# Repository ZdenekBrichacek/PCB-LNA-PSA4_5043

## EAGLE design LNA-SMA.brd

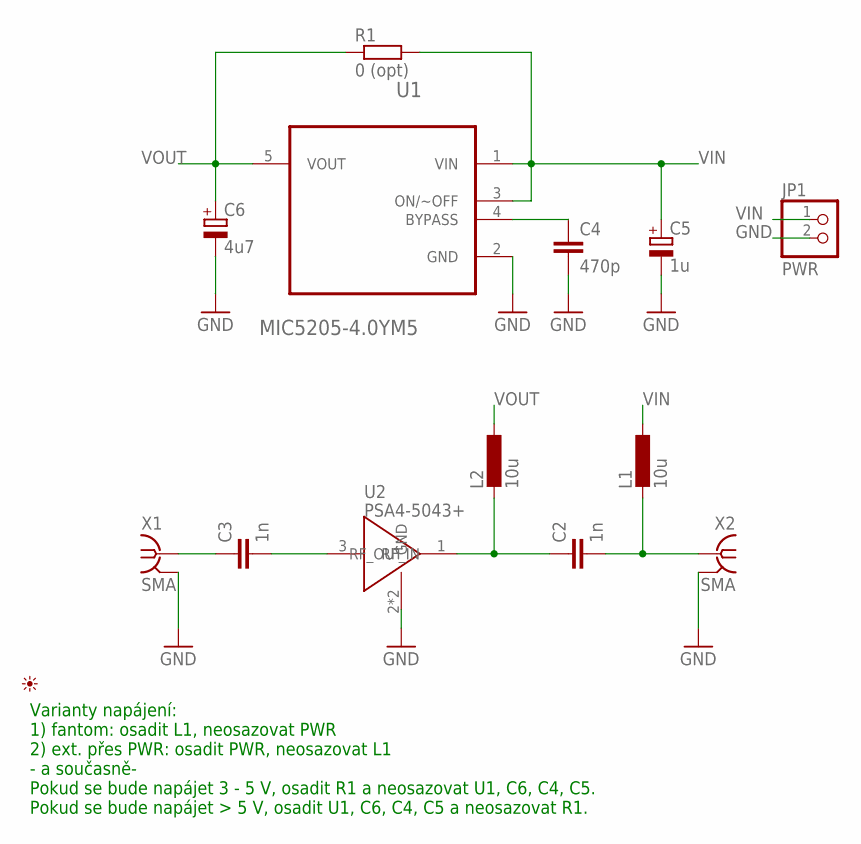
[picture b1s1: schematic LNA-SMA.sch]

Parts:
C2, C3: 1n; C0603
C4: 470p; C0603
C5: 1u; SMC_A
C6: 4u7; SMC_A
JP1: PWR; 1X02
L1, L2: 10u; L2012C
R1: 0 (opt); R0603
U1: MIC5205-4.0YM5; SOT95P280X145-5N
U2: PSA4-5043+; INF-SOT343_V_1PRIMARY
U$1: PICTO_1
X1, X2: SMA; J502-ND-142-0701-801/806

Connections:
GND: C4.2, C5.-, C6.-, JP1.2, U1.2 (GND), U2.2 (GND), U2.4 (GND), X1.G@1 (2), X1.G@2 (2), X1.G@3 (2), X1.G@4 (2), X2.G@1 (2), X2.G@2 (2), X2.G@3 (2), X2.G@4 (2)
unnamed: C4.1, U1.4 (BYPASS)
unnamed: C3.2, U2.3 (RF_IN)
unnamed: C2.1, L2.2, U2.1 (RF_OUT)
RF_IN: C2.2, L1.2, X2.1
RF_OUT: C3.1, X1.1
VIN: C5.+, JP1.1, L1.1, R1.2, U1.1 (VIN), U1.3 (ON/~OFF)
VOUT: C6.+, L2.1, R1.1, U1.5 (VOUT)

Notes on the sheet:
Varianty napájení: 1) fantom: osadit L1, neosazovat PWR 2) ext. přes PWR: osadit PWR, neosazovat L1 - a současně- Pokud se bude napájet 3 - 5 V, osadit R1 a neosazovat U1, C6, C4, C5. Pokud se bude napájet > 5 V, osadit U1, C6, C4, C5 a neosazovat R1.

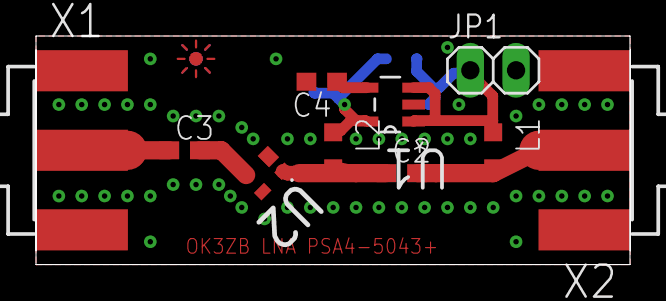
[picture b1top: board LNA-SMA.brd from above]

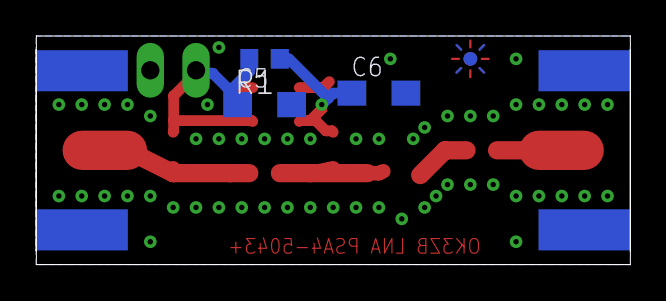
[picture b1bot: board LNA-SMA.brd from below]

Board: 2 copper layers, 33.0 x 12.7 mm, 14 parts (3 on the bottom side), 8 nets.

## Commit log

2017-10-10 :octocat: Added .gitattributes & .gitignore files
2017-10-10 Initial version
